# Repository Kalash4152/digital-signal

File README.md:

⏱️🔼 Digital Staircase Waveform Generator for DSO – A System-Level Design Approach 💡⚙️
🧠 Problem Statement
In traditional Digital Storage Oscilloscopes (DSOs), the Time/Division control knob plays a crucial role in adjusting the horizontal sweep rate — essentially, it defines how fast the waveform scrolls across the screen. But what if we could digitally replace this analog knob?

👨‍🔧 Mr. Suresh and his engineering team at eXFac Systems were tasked with redesigning this Time/Division control section using pre-designed functional blocks. Their mission:
🔧 Integrate the blocks to generate a staircase waveform that acts as the new control signal, where the speed of waveform steps represents the time/division setting.
🧮 A pair of 7-segment displays shows the step frequency — a fast count = high frequency, and a slow count = low frequency.

They had to:

Use 8 digital inputs (representing binary values).

Generate a staircase waveform from those inputs.

Replace analog functionality with digital blocks.

Display the frequency visually on 7-segment displays.

Optimize power supply use.

Identify and discard redundant modules.

Verify the waveform using simulation and theory.

Finally, design a PCB layout for real-world implementation!

🛠️ Solution Overview
To solve the above challenge, we designed a complete digital system that mimics analog waveform generation through logic components, as described below 👇:

📦 Block-Level Flow
css
Copy
Edit
[8 Switches] → [2x 4029 Binary Counters] → [DAC0808] → [Op-Amp (LM741)] → [Staircase Waveform Output]
                                           ↓
                                    [7-Segment Drivers] → [Displays]
🔍 Component-Wise Explanation
🔘 8 Logic Switches (Manual Input)
These act as binary control signals, simulating values between 0 and 255. You can change frequency by altering the binary input values (just like turning a knob!). Each bit represents part of the input to the counter.

🔢 4029 Binary Up Counters (U2 & U7)
The heart of the system — two CD4029 counters are used in cascade mode to generate a binary count that ranges from 0 to 255.
🔁 They are clocked by a NE555 timer (U10), and every pulse increments the counter by 1.

🧮 DAC0808 (U6)
The Digital-to-Analog Converter takes 8-bit binary data and generates a proportional analog current.
This current output is not directly usable, so we convert it into voltage using...

🎛️ Op-Amp (LM741)
The Op-Amp converts the current from DAC into a staircase-shaped voltage waveform 🪜. Each clock pulse results in a small voltage jump, forming the characteristic staircase shape over time.

⏰ NE555 Timer (U10)
This classic IC is used as a clock generator for the counters. By varying R and C values, you can change the frequency of pulses.
👉 Faster clock = faster waveform stepping = higher frequency display.

📟 7-Segment Display (Driven by 4511 BCD to 7-Segment Decoders)
The outputs of the 4029 counters are also connected to BCD to 7-segment decoders (U8 & U9) which then drive the displays.
This gives a real-time visual feedback of the frequency or step count.

🔋 Power Supply
Efficient usage of available DC sources:

+5V for logic ICs like counters, DAC, display drivers.

+12V and -12V for analog sections like Op-Amps and DAC reference voltages.

⚙️ Working Principle
Switches feed binary input to the counter chain.

NE555 provides clock pulses to increment the counters.

Counter outputs feed the DAC, creating a stepped analog output.

Op-Amp converts DAC current into a staircase voltage waveform.

Counter values are also sent to 7-segment displays to indicate step count (linked to waveform frequency).

Result: A dynamic, digitally controlled staircase waveform replaces the analog Time/Division knob of the DSO! 🔄

📊 Simulations & Testing
✔️ Simulated in Proteus to validate the waveform.
✔️ Output verified with numerical calculations for DAC resolution and timing.
✔️ Output compared with analog knob output profile.

🖨️ PCB Design
The final goal is to design and fabricate a PCB with optimized power layout, IC placements, and waveform output routing — making it ready for hardware deployment in future scope of DSO redesigns!

💡 Applications & Future Scope
📡 Oscilloscope development and instrumentation.

👨‍🏫 Digital electronics lab experiments.

🧪 DAC/ADC concept learning.

🔁 Replace any analog knob with a digitally controlled waveform output!

🌟 Highlights
🚀 Fully functional digital-to-analog waveform conversion.

🧠 Concepts used: Digital Counters, DAC, Op-Amps, Timers, Displays.

🧰 Tool: Proteus 8.12+, easy to simulate and test.

🔌 Efficient power supply integration (+5V, ±12V).

✅ Beginner-friendly logic but powerful concept application.

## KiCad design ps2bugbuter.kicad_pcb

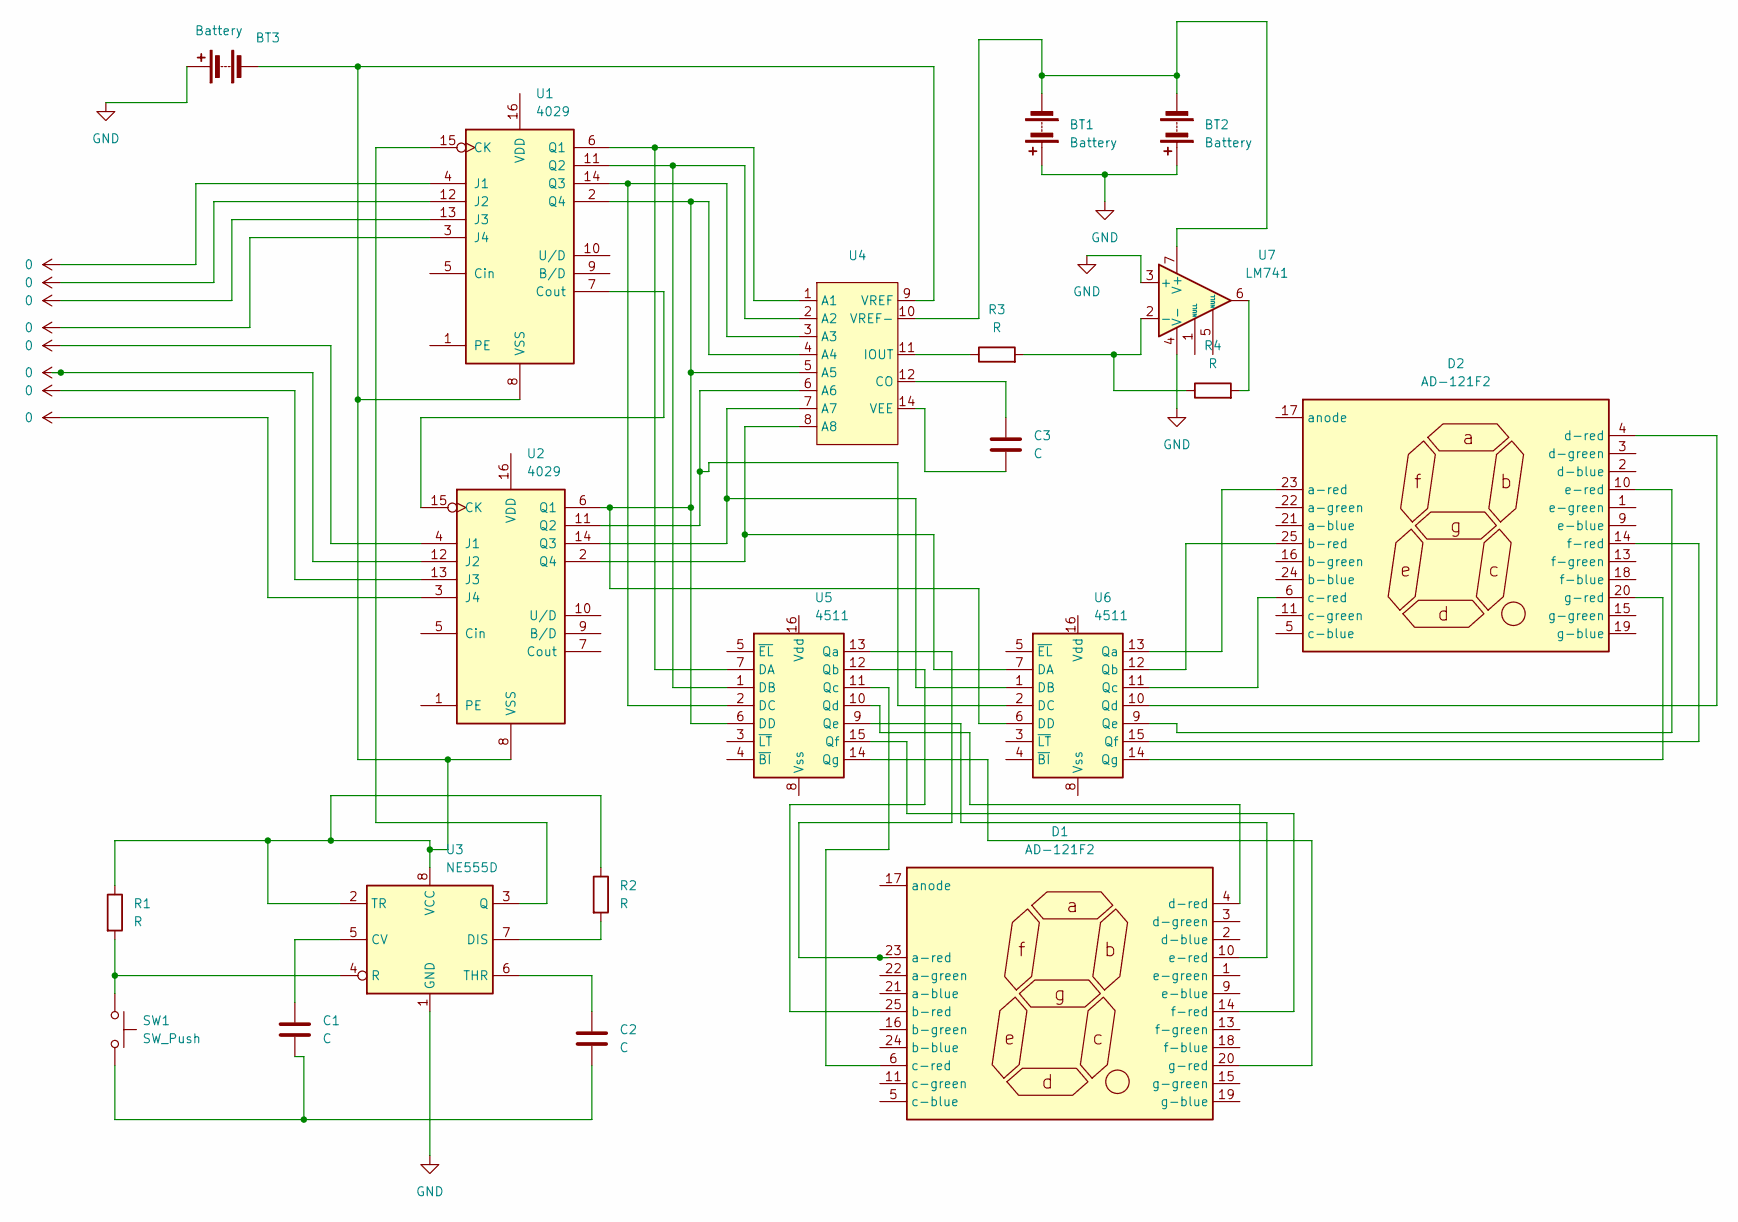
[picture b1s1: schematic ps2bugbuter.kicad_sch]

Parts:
BT1, BT2, BT3: Battery; BatteryHolder_LINX_BAT-HLD-012-SMT
C1, C2, C3: C; CP_Elec_4x5.8
D1, D2: AD-121F2
R1, R2, R3, R4: R; R_0805_2012Metric_Pad1.20x1.40mm_HandSolder
SW1: SW_Push; Panasonic_EVQPUM_EVQPUD
U1, U2: 4029; PinSocket_1x16_P2.54mm_Horizontal
U3: NE555D; SOIC-8_3.9x4.9mm_P1.27mm
U4: PinSocket_1x16_P2.54mm_Horizontal
U5, U6: 4511; PinSocket_1x16_P2.54mm_Horizontal
U7: LM741; PinSocket_1x08_P2.54mm_Vertical_SMD_Pin1Right

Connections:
0: U1.3 (J4), U1.4 (J1), U1.12 (J2), U1.13 (J3), U2.3 (J4), U2.4 (J1), U2.12 (J2), U2.13 (J3)
GND: BT1.1 (+), BT2.1 (+), BT3.1 (+), U3.1 (GND), U7.3 (+), U7.4 (V-)
unnamed: BT1.2 (-), BT2.2 (-), U4.10 (VREF-), U7.7 (V+)
unnamed: BT3.2 (-), R1.1, R2.1, U1.8 (VSS), U2.8 (VSS), U3.2 (TR), U3.8 (VCC), U4.9 (VREF)
unnamed: C1.2, C2.2, SW1.2
unnamed: D1.23 (a-red), U5.13 (Qa)
unnamed: D1.25 (b-red), U5.12 (Qb)
unnamed: D1.6 (c-red), U5.11 (Qc)
unnamed: D1.4 (d-red), U5.10 (Qd)
unnamed: D1.10 (e-red), U5.9 (Qe)
unnamed: D1.14 (f-red), U5.15 (Qf)
unnamed: D1.20 (g-red), U5.14 (Qg)
unnamed: D2.23 (a-red), U6.13 (Qa)
unnamed: D2.25 (b-red), U6.12 (Qb)
unnamed: D2.6 (c-red), U6.11 (Qc)
unnamed: D2.4 (d-red), U6.10 (Qd)
unnamed: D2.10 (e-red), U6.9 (Qe)
unnamed: D2.14 (f-red), U6.15 (Qf)
unnamed: D2.20 (g-red), U6.14 (Qg)
unnamed: R4.2, U7.6
unnamed: U1.15 (CK), U3.3 (Q)
unnamed: U1.7 (Cout), U2.15 (CK)
unnamed: U1.6 (Q1), U4.1 (A1), U5.7 (DA)
unnamed: U1.11 (Q2), U4.2 (A2), U5.1 (DB)
unnamed: U1.14 (Q3), U4.3 (A3), U5.2 (DC)
unnamed: U1.2 (Q4), U2.6 (Q1), U4.4 (A4), U4.5 (A5), U5.6 (DD), U6.6 (DD)
unnamed: U2.11 (Q2), U4.6 (A6), U6.2 (DC)
unnamed: U2.14 (Q3), U4.7 (A7), U6.1 (DB)
unnamed: U2.2 (Q4), U4.8 (A8), U6.7 (DA)
unnamed: C1.1, U3.5 (CV)
unnamed: R2.2, U3.7 (DIS)
unnamed: R1.2, SW1.1, U3.4 (R)
unnamed: C2.1, U3.6 (THR)
unnamed: C3.1, U4.12 (CO)
unnamed: R3.1, U4.11 (IOUT)
unnamed: C3.2, U4.14 (VEE)
unnamed: R3.2, R4.1, U7.2 (-)

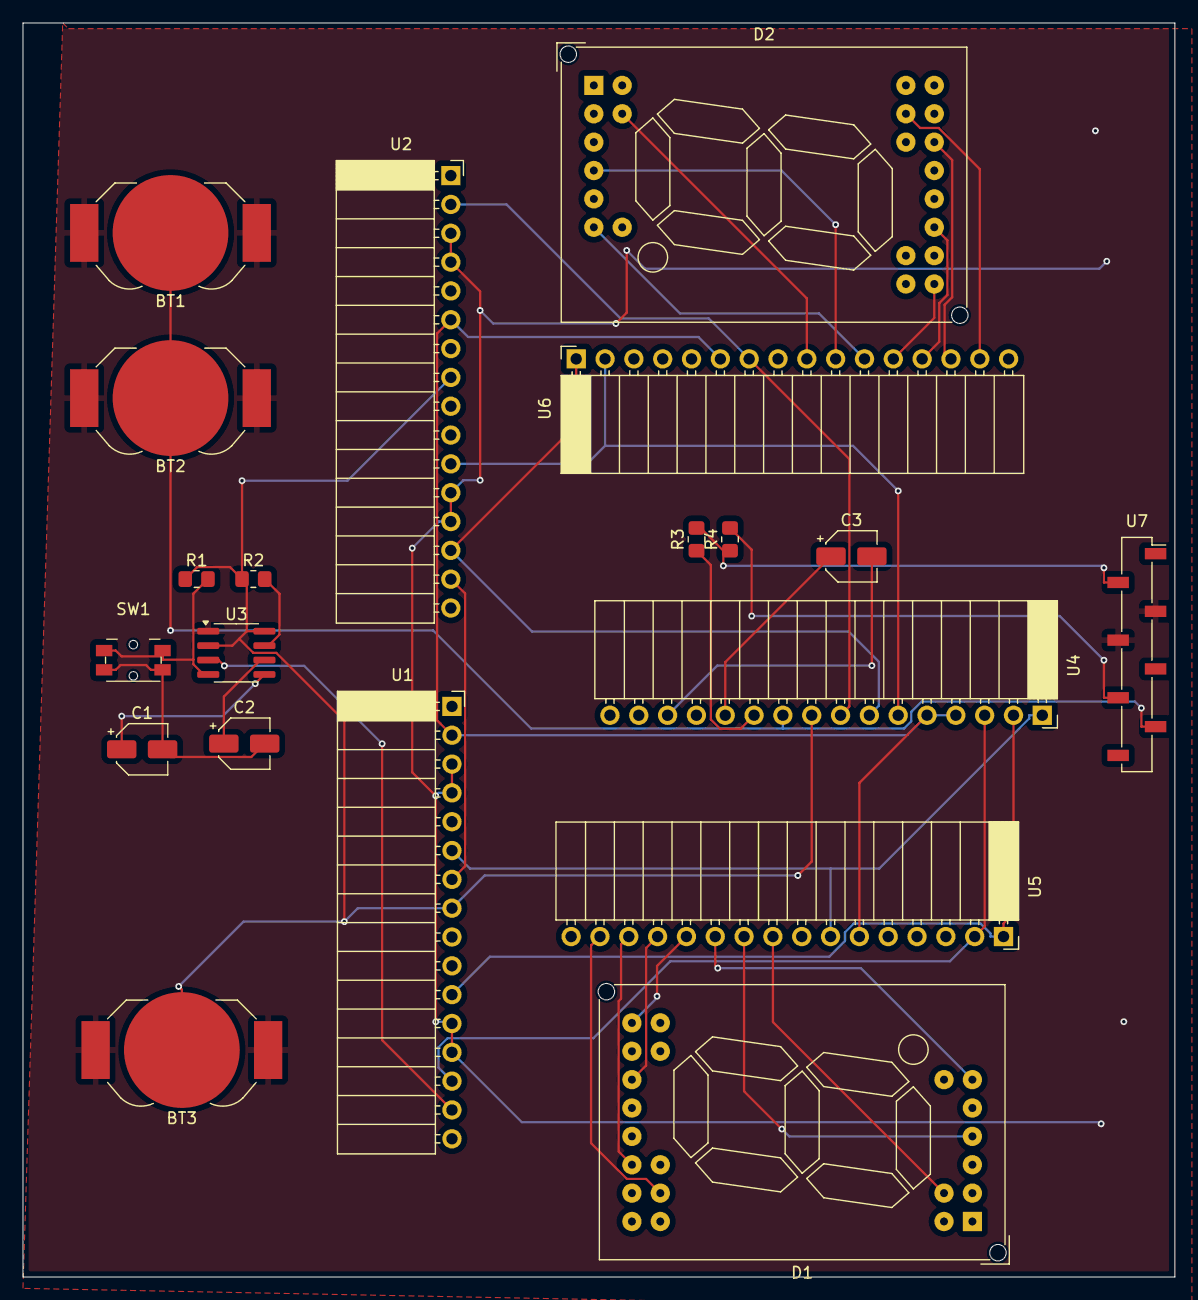
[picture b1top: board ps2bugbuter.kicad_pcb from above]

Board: 2 copper layers, 101.5 x 110.5 mm, 20 parts (0 on the bottom side), 37 nets.

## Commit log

2025-06-09 Add files via upload
    ⏱️🔼 Digital Staircase Waveform Generator for DSO – A System-Level Design Approach 💡⚙️
    🧠 Problem Statement
    In traditional Digital Storage Oscilloscopes (DSOs), the Time/Division control knob plays a crucial role in adjusting the horizontal sweep rate — essentially, it defines how fast the waveform scrolls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
    👨‍🔧 Mr. Suresh and his engineering team at eXFac Systems were tasked with redesigning this Time/Division control section using pre-designed functional blocks. Their mission:
    🔧 Integrate the blocks to generate a staircase waveform that acts as the new control
